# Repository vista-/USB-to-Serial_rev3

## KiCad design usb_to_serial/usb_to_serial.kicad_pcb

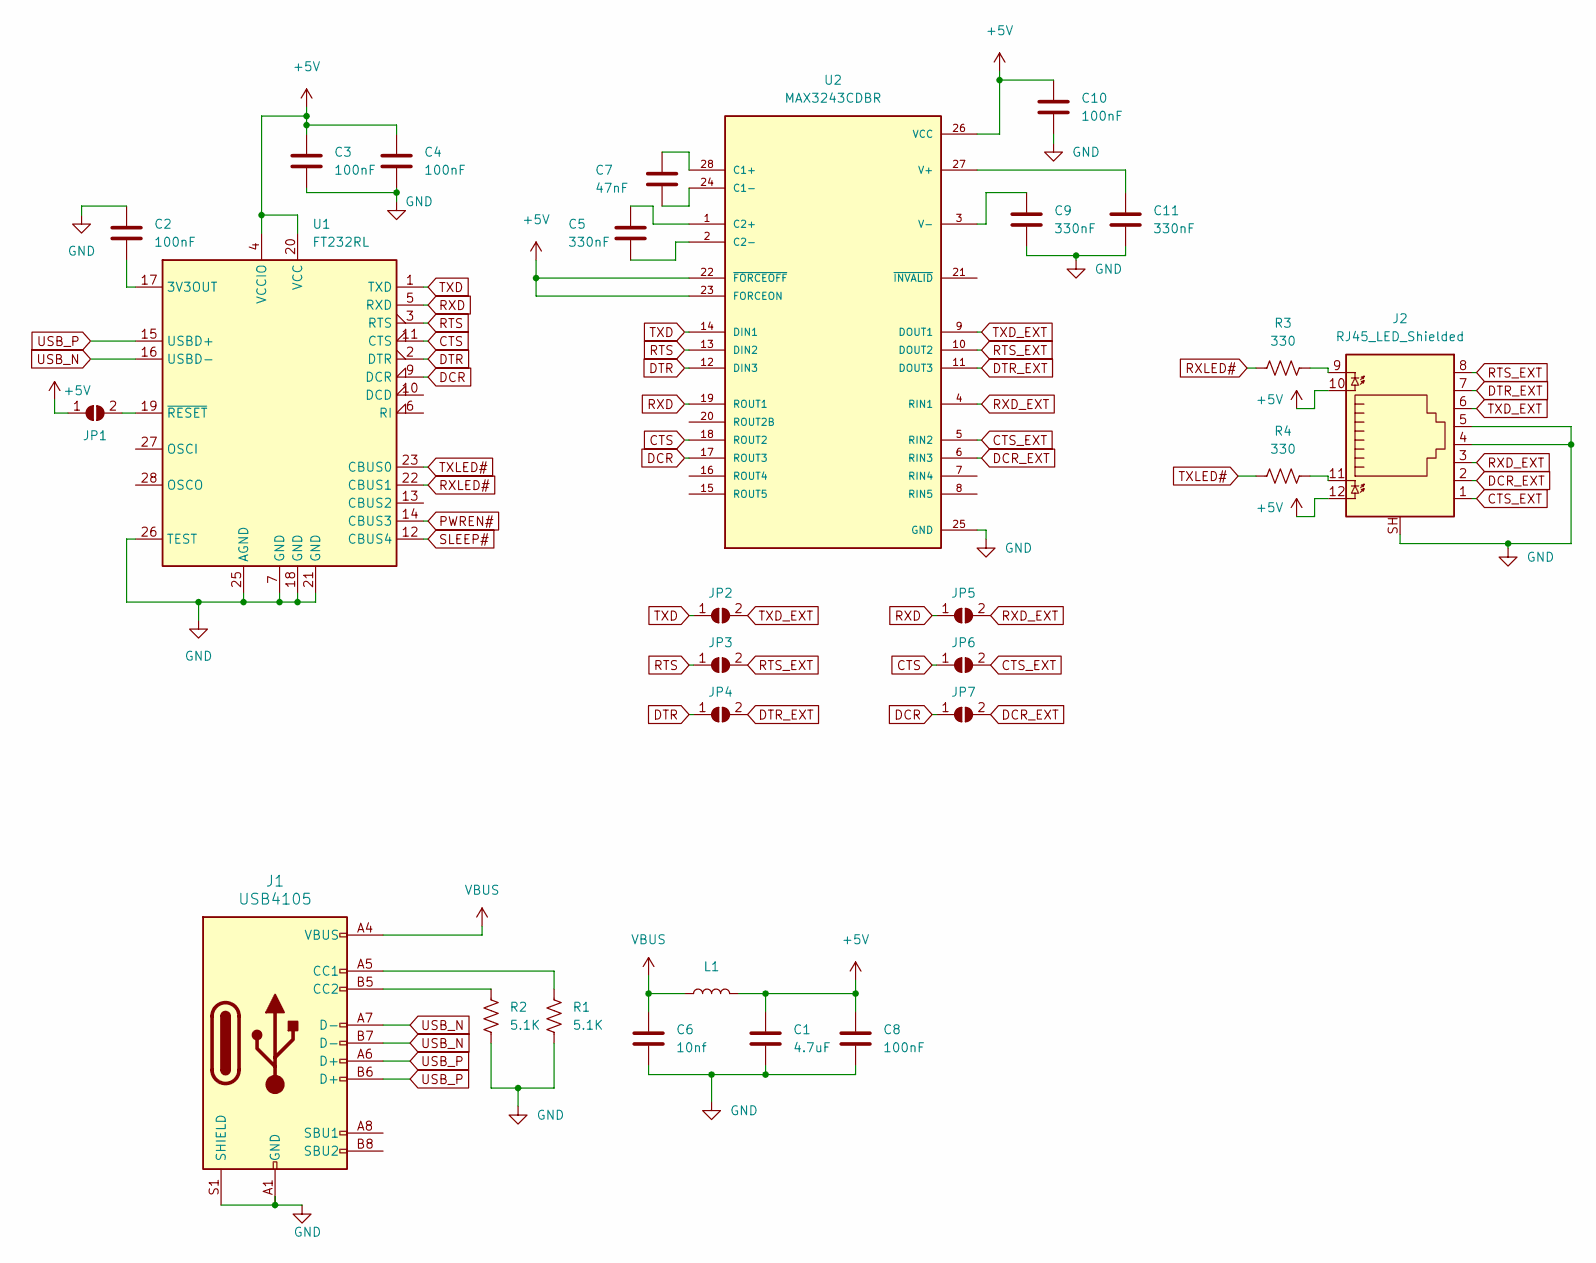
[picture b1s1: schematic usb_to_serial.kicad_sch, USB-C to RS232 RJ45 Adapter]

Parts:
C1: 4.7uF; C_1206_3216Metric_Pad1.33x1.80mm_HandSolder
C2, C3, C4, C8, C10: 100nF; C_0603_1608Metric_Pad1.08x0.95mm_HandSolder
C5, C9, C11: 330nF; C_0603_1608Metric_Pad1.08x0.95mm_HandSolder
C6: 10nf; C_0603_1608Metric_Pad1.08x0.95mm_HandSolder
C7: 47nF; C_0603_1608Metric_Pad1.08x0.95mm_HandSolder
J1: USB4105; USB_C_Receptacle_HRO_TYPE-C-31-M-12; PARTREV B3
J2: RJ45_LED_Shielded; RJ45_Amphenol_RJHSE538X
JP1, JP2, JP3, JP4, JP5, JP6, JP7: SolderJumper_2_Open; SolderJumper-2_P1.3mm_Open_RoundedPad1.0x1.5mm
L1: L; L_0805_2012Metric_Pad1.15x1.40mm_HandSolder
R1, R2: 5.1K; R_0603_1608Metric_Pad0.98x0.95mm_HandSolder
R3, R4: 330; R_0603_1608Metric_Pad0.98x0.95mm_HandSolder
U1: FT232RL; SSOP-28_5.3x10.2mm_P0.65mm
U2: MAX3243CDBR; SSOP-28_5.3x10.2mm_P0.65mm

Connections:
+5V: C1.1, C3.1, C4.1, C8.1, C10.1, J2.10, J2.12, JP1.1 (A), L1.2, U1.4 (VCCIO), U1.20 (VCC), U2.22 (~FORCEOFF), U2.23 (FORCEON), U2.26 (VCC)
CTS: JP6.1 (A), U1.11 (CTS), U2.18 (ROUT2)
CTS_EXT: J2.1, JP6.2 (B), U2.5 (RIN2)
DCR: JP7.1 (A), U1.9 (DCR), U2.17 (ROUT3)
DCR_EXT: J2.2, JP7.2 (B), U2.6 (RIN3)
DTR: JP4.1 (A), U1.2 (DTR), U2.12 (DIN3)
DTR_EXT: J2.7, JP4.2 (B), U2.11 (DOUT3)
GND: C1.2, C2.1, C3.2, C4.2, C6.2, C8.2, C9.2, C10.2, C11.2, J1.A1 (GND), J1.A12 (GND), J1.B1 (GND), J1.B12 (GND), J1.S1 (SHIELD), J2.4, J2.5, J2.SH, R1.2, R2.2, U1.7 (GND), U1.18 (GND), U1.21 (GND), U1.25 (AGND), U1.26 (TEST), U2.25 (GND)
unnamed: J1.A5 (CC1), R1.1
unnamed: J1.B5 (CC2), R2.1
unnamed: J2.9, R3.2
unnamed: J2.11, R4.2
unnamed: JP1.2 (B), U1.19 (~RESET)
unnamed: C2.2, U1.17 (3V3OUT)
unnamed: C7.1, U2.28 (C1+)
unnamed: C7.2, U2.24 (C1-)
unnamed: C5.1, U2.1 (C2+)
unnamed: C5.2, U2.2 (C2-)
unnamed: C11.1, U2.27 (V+)
unnamed: C9.1, U2.3 (V-)
PWREN#: U1.14 (CBUS3)
RTS: JP3.1 (A), U1.3 (RTS), U2.13 (DIN2)
RTS_EXT: J2.8, JP3.2 (B), U2.10 (DOUT2)
RXD: JP5.1 (A), U1.5 (RXD), U2.19 (ROUT1)
RXD_EXT: J2.3, JP5.2 (B), U2.4 (RIN1)
RXLED#: R3.1, U1.22 (CBUS1)
SLEEP#: U1.12 (CBUS4)
TXD: JP2.1 (A), U1.1 (TXD), U2.14 (DIN1)
TXD_EXT: J2.6, JP2.2 (B), U2.9 (DOUT1)
TXLED#: R4.1, U1.23 (CBUS0)
USB_N: J1.A7 (D-), J1.B7 (D-), U1.16 (USBD-)
USB_P: J1.A6 (D+), J1.B6 (D+), U1.15 (USBD+)
VBUS: C6.1, J1.A4 (VBUS), J1.A9 (VBUS), J1.B4 (VBUS), J1.B9 (VBUS), L1.1

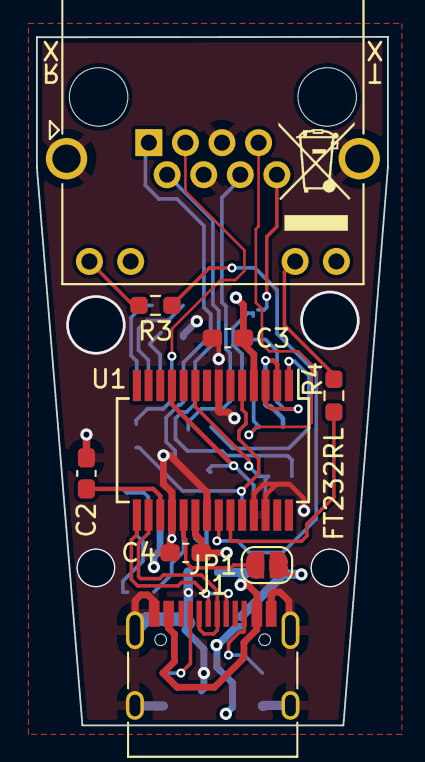
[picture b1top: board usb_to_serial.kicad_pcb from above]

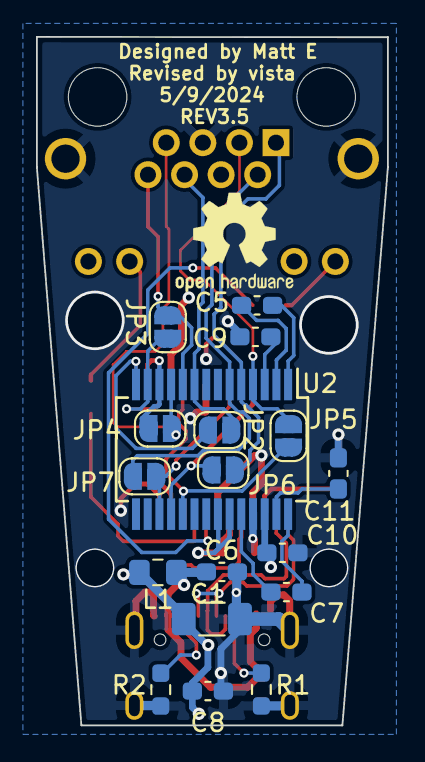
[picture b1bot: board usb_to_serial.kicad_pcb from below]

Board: 4 copper layers, 19.5 x 38.2 mm, 27 parts (18 on the bottom side), 31 nets.

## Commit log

2022-05-29 Board Order
2024-05-08 Revision for Aisler design rules
2024-05-09 Change USB-C connector footprint with one with NPTHs, add connections for forceon/forceoff on MAX3243
2024-12-29 Add iBOM
